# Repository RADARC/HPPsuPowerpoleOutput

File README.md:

# HPPsuPowerpoleOutput

This is a PCB designed to connect to the backplane of a HP server HSTNS-PD18 or HSTNS-PL18 power supply and provide powerpole outputs.
Please see https://www.qsl.net/gm0onx/SMPU.htm for instructions on how to modify these power supplies to increase the main output up to 13.5V.

# Parts
* 64 pin 2.54mm pitch edge connector. I got a pack of 5 from Aliexpress for about £7.50
* D1/2 standard 5mm led's
* Vertical pcb mount powerpole contacts and shells
* R1 - 22k Resistor
* R2/3 - 2k2 Resistor
* 3mm SPDT slide switch (e.g https://amzn.eu/d/0gzYgMrN)

# Notes

# Versions

# Current status
PCB complete. Case complete.

# 3D case
https://www.printables.com/model/1689658-hp-server-psu-powerpole-output

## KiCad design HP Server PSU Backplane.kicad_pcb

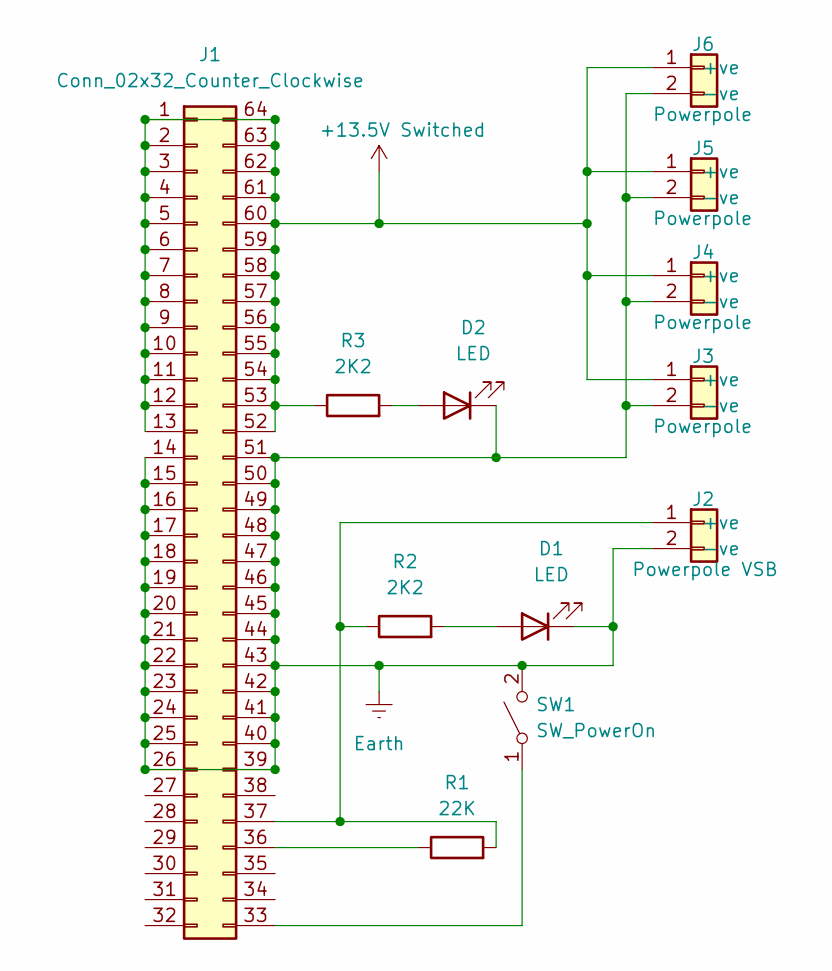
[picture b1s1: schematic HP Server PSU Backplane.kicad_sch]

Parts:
D1, D2: LED; LED_D5.0mm
J1: Conn_02x32_Counter_Clockwise; Edge_Socket_2x32_2.54mm_5.08mm_ccw
J2: Powerpole VSB; Anderson_Powerpole_2w
J3, J4, J5, J6: Powerpole; Anderson_Powerpole_2w
R1: 22K; R_Axial_DIN0207_L6.3mm_D2.5mm_P7.62mm_Horizontal
R2, R3: 2K2; R_Axial_DIN0207_L6.3mm_D2.5mm_P7.62mm_Horizontal
SW1: SW_PowerOn; PinHeader_1x02_P2.54mm_Vertical

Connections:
+13.5V Switched: J1.1, J1.2, J1.3, J1.4, J1.5, J1.6, J1.7, J1.8, J1.9, J1.10, J1.11, J1.12, J1.13, J1.52, J1.53, J1.54, J1.55, J1.56, J1.57, J1.58, J1.59, J1.60, J1.61, J1.62, J1.63, J1.64, J3.1 (+ve), J4.1 (+ve), J5.1 (+ve), J6.1 (+ve), R3.1
Earth: D1.1 (K), D2.1 (K), J1.14, J1.15, J1.16, J1.17, J1.18, J1.19, J1.20, J1.21, J1.22, J1.23, J1.24, J1.25, J1.26, J1.39, J1.40, J1.41, J1.42, J1.43, J1.44, J1.45, J1.46, J1.47, J1.48, J1.49, J1.50, J1.51, J2.2 (-ve), J3.2 (-ve), J4.2 (-ve), J5.2 (-ve), J6.2 (-ve), SW1.2 (B)
unnamed: D1.2 (A), R2.2
unnamed: D2.2 (A), R3.2
unnamed: J1.33, SW1.1 (A)
unnamed: J1.36, R1.1
unnamed: J1.37, J2.1 (+ve), R1.2, R2.1

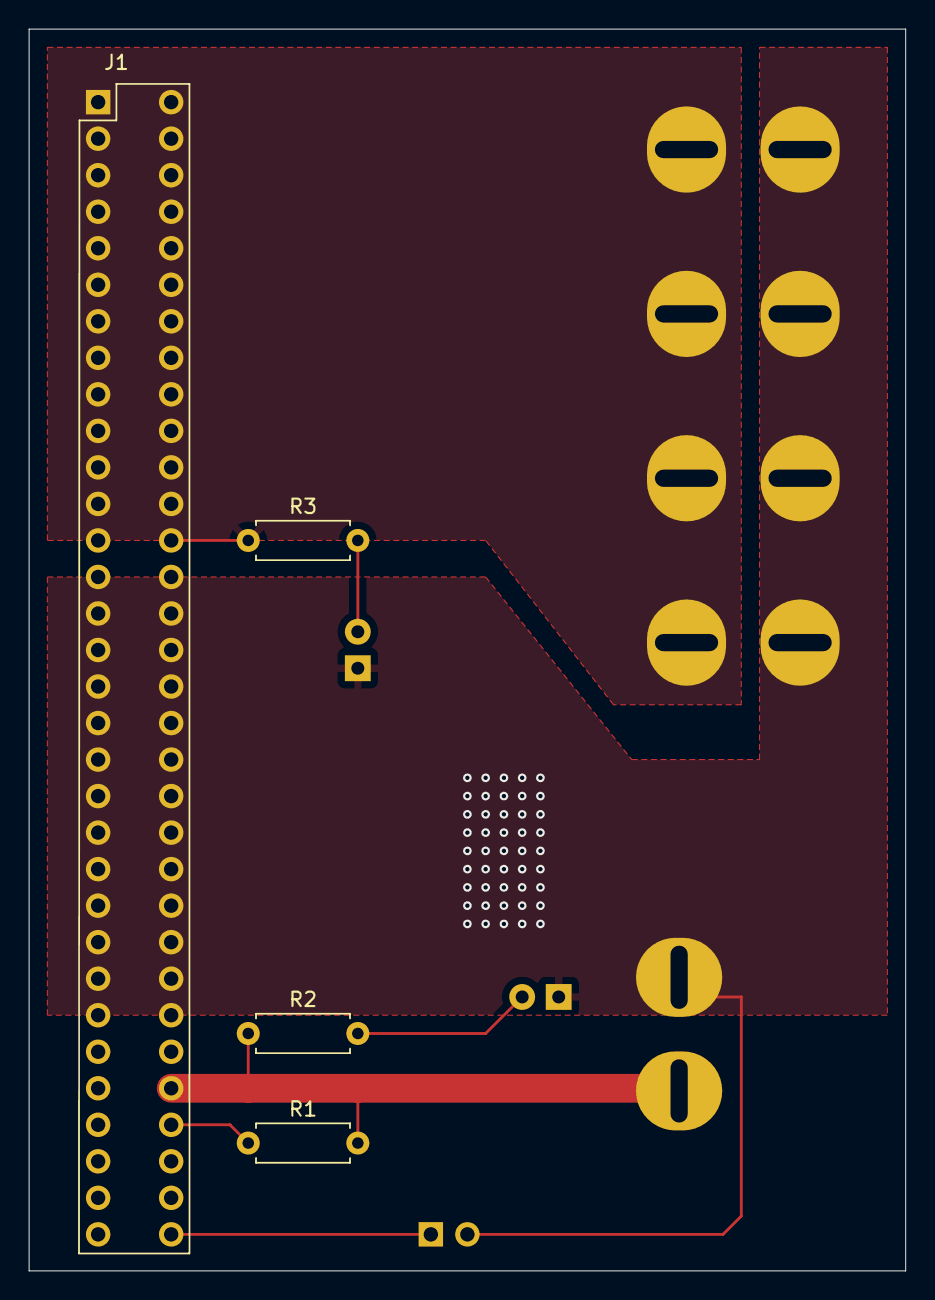
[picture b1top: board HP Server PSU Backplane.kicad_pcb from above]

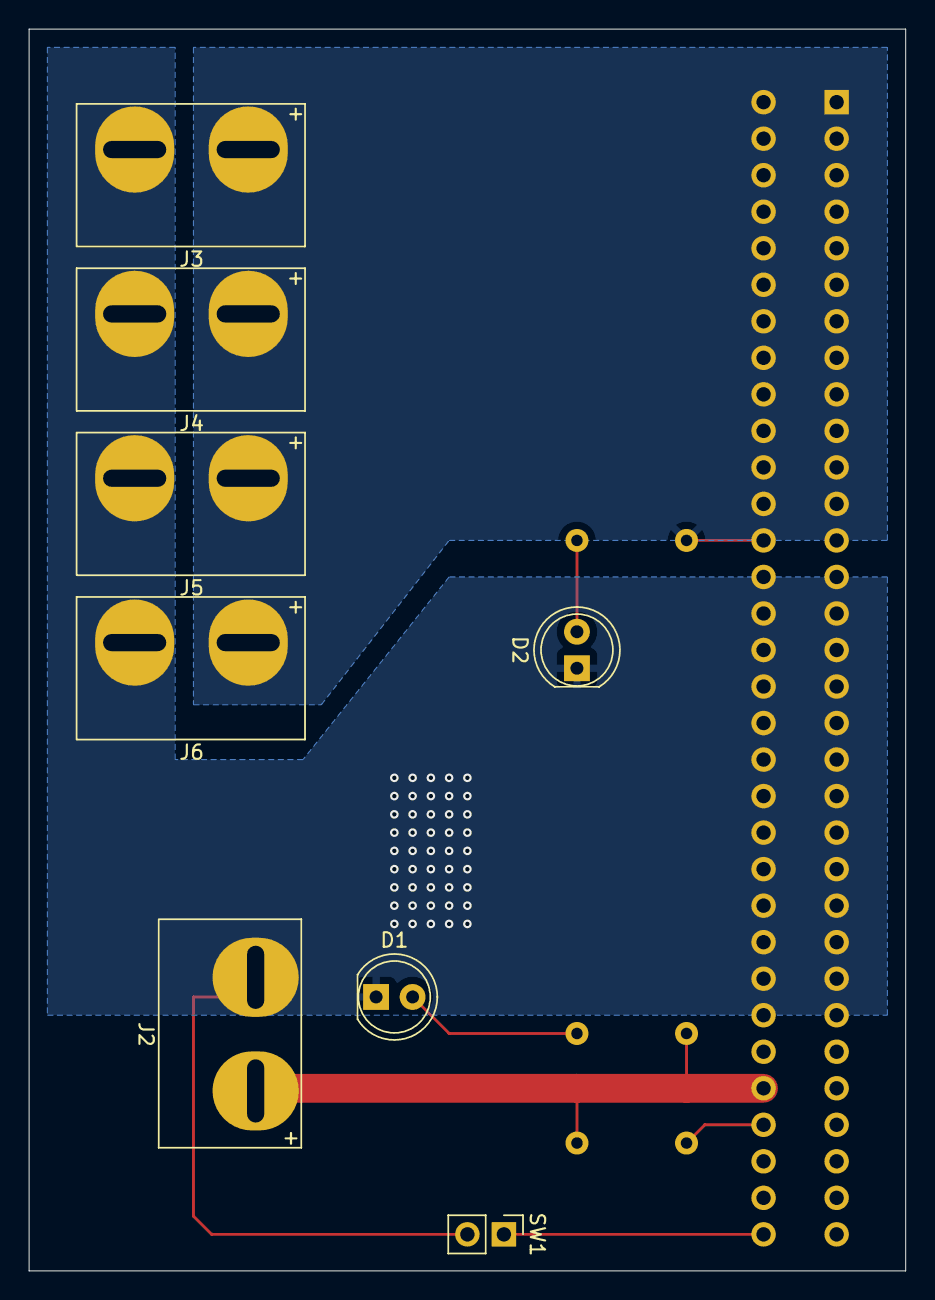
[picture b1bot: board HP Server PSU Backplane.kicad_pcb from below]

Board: 2 copper layers, 61.0 x 86.4 mm, 12 parts (8 on the bottom side), 7 nets.

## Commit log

2026-04-14 initial load
